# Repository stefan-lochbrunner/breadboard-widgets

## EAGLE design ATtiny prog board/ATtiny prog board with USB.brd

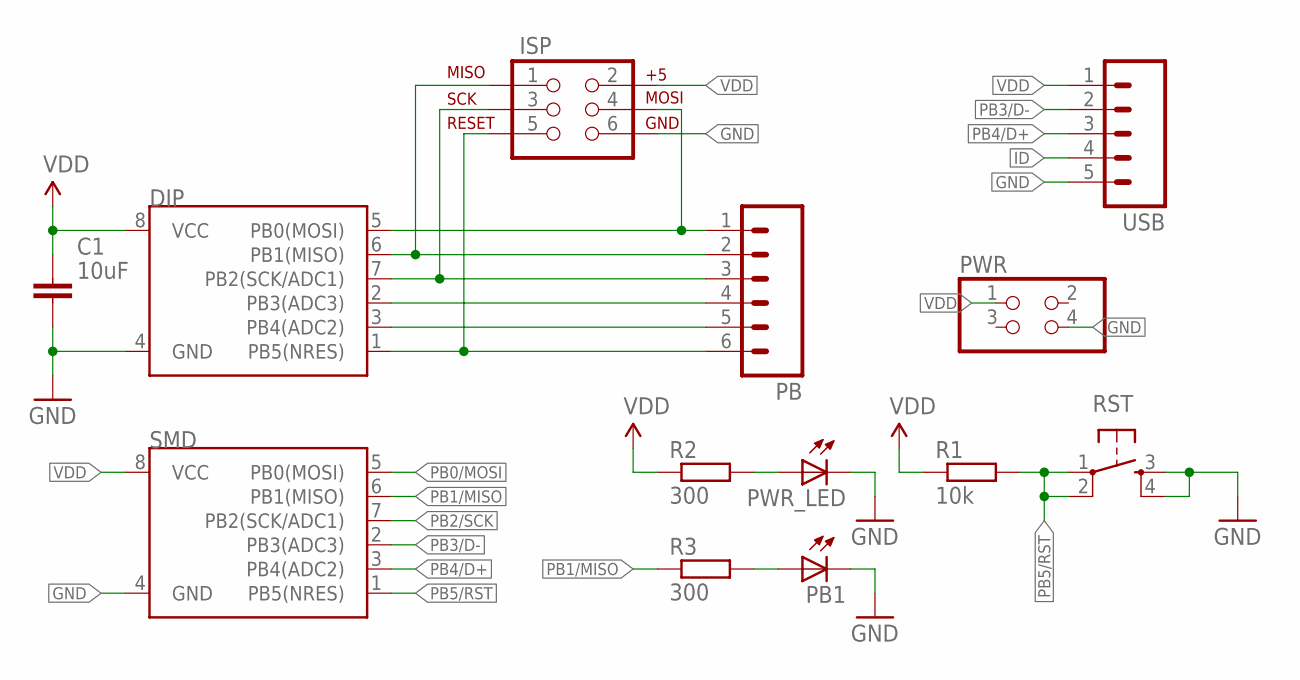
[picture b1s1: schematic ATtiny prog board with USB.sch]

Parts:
C1: 10uF; C805
DIP: ATTINY45TINY85-20-DIP; DIP08
ISP: AVR_SPI_PRG_6PTH; 2X3
PB: M06SILK_FEMALE_PTH; 1X06
PB1: LED-0805; LED-805
PWR: PINHD-2X2; 2X02
PWR_LED: LED-0805; LED-805
R1: 10k; R603
R2, R3: 300; R603
RST: TAC_SWITCHPTH; TACTILE-PTH
SMD: ATTINY45TINY85-20-SMT; SO08-EIAJ
USB: M05PTH; 1X05

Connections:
GND: C1.2, DIP.4 (GND), ISP.6, PB1.C, PWR.4, PWR_LED.C, RST.3, RST.4, SMD.4 (GND), USB.5
ID: USB.4
unnamed: PWR_LED.A, R2.2
unnamed: PB1.A, R3.2
PB0/MOSI: DIP.5 (PB0(MOSI)), ISP.4, PB.1, SMD.5 (PB0(MOSI))
PB1/MISO: DIP.6 (PB1(MISO)), ISP.1, PB.2, R3.1, SMD.6 (PB1(MISO))
PB2/SCK: DIP.7 (PB2(SCK/ADC1)), ISP.3, PB.3, SMD.7 (PB2(SCK/ADC1))
PB3/D-: DIP.2 (PB3(ADC3)), PB.4, SMD.2 (PB3(ADC3)), USB.2
PB4/D+: DIP.3 (PB4(ADC2)), PB.5, SMD.3 (PB4(ADC2)), USB.3
PB5/RST: DIP.1 (PB5(NRES)), ISP.5, PB.6, R1.2, RST.1, RST.2, SMD.1 (PB5(NRES))
VDD: C1.1, DIP.8 (VCC), ISP.2, PWR.1, R1.1, R2.1, SMD.8 (VCC), USB.1

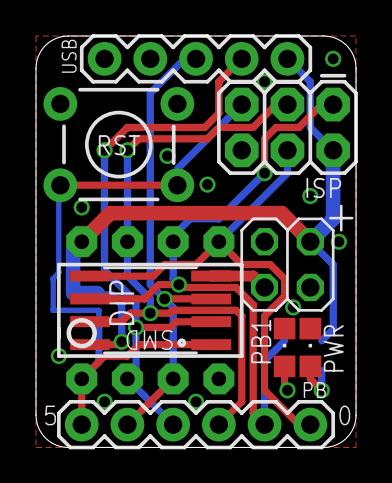
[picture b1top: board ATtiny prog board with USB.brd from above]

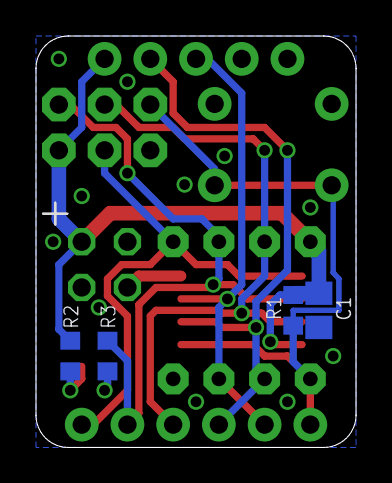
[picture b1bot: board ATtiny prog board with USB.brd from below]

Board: 2 copper layers, 17.8 x 22.9 mm, 13 parts (4 on the bottom side), 10 nets.

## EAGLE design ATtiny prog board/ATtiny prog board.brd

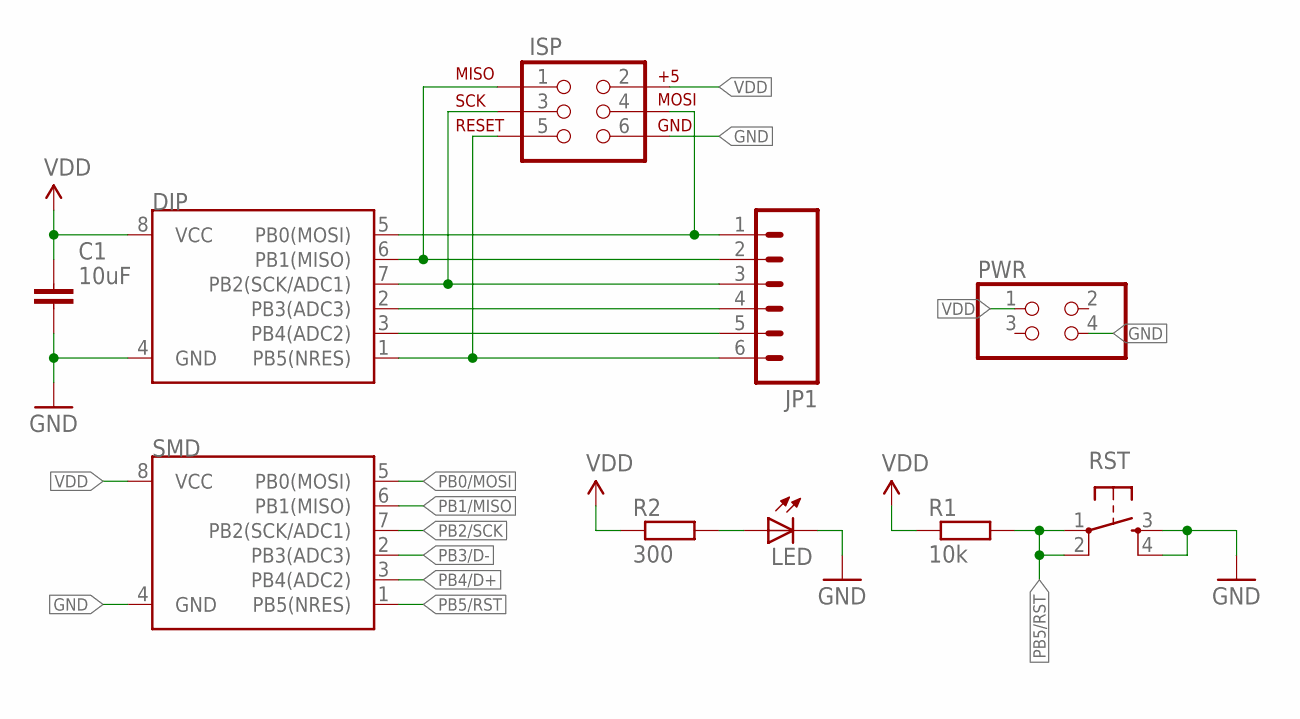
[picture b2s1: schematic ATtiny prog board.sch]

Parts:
C1: 10uF; C805
DIP: ATTINY45TINY85-20-DIP; DIP08
ISP: AVR_SPI_PRG_6PTH; 2X3
JP1: M06SILK_FEMALE_PTH; 1X06
LED: LED-0603; LED-603
PWR: PINHD-2X2; 2X02
R1: 10k; R603
R2: 300; R603
RST: TAC_SWITCHPTH; TACTILE-PTH
SMD: ATTINY45TINY85-20-SMT; SO08-EIAJ

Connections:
GND: C1.2, DIP.4 (GND), ISP.6, LED.C, PWR.4, RST.3, RST.4, SMD.4 (GND)
unnamed: LED.A, R2.2
PB0/MOSI: DIP.5 (PB0(MOSI)), ISP.4, JP1.1, SMD.5 (PB0(MOSI))
PB1/MISO: DIP.6 (PB1(MISO)), ISP.1, JP1.2, SMD.6 (PB1(MISO))
PB2/SCK: DIP.7 (PB2(SCK/ADC1)), ISP.3, JP1.3, SMD.7 (PB2(SCK/ADC1))
PB3/D-: DIP.2 (PB3(ADC3)), JP1.4, SMD.2 (PB3(ADC3))
PB4/D+: DIP.3 (PB4(ADC2)), JP1.5, SMD.3 (PB4(ADC2))
PB5/RST: DIP.1 (PB5(NRES)), ISP.5, JP1.6, R1.2, RST.1, RST.2, SMD.1 (PB5(NRES))
VDD: C1.1, DIP.8 (VCC), ISP.2, PWR.1, R1.1, R2.1, SMD.8 (VCC)

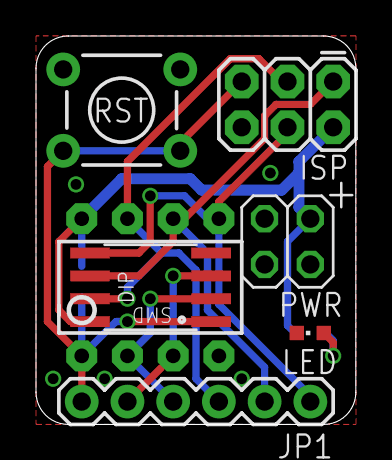
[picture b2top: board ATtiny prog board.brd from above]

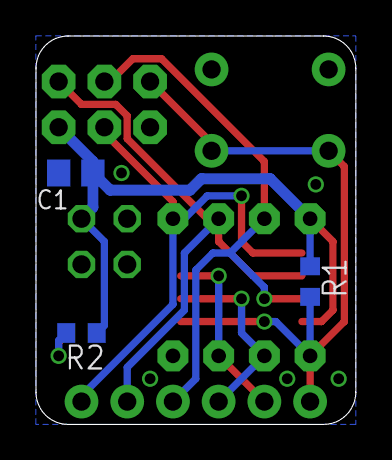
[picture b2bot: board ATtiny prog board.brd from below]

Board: 2 copper layers, 17.8 x 21.6 mm, 10 parts (3 on the bottom side), 9 nets.

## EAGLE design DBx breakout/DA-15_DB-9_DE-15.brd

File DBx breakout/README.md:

Simple breakout for DA-15, DB/DE-9 & DE-15(VGA) connectors. DB-9 to be placed on DA-15 footprint. [**more info**](https://hackaday.io/project/6332/log/26554)

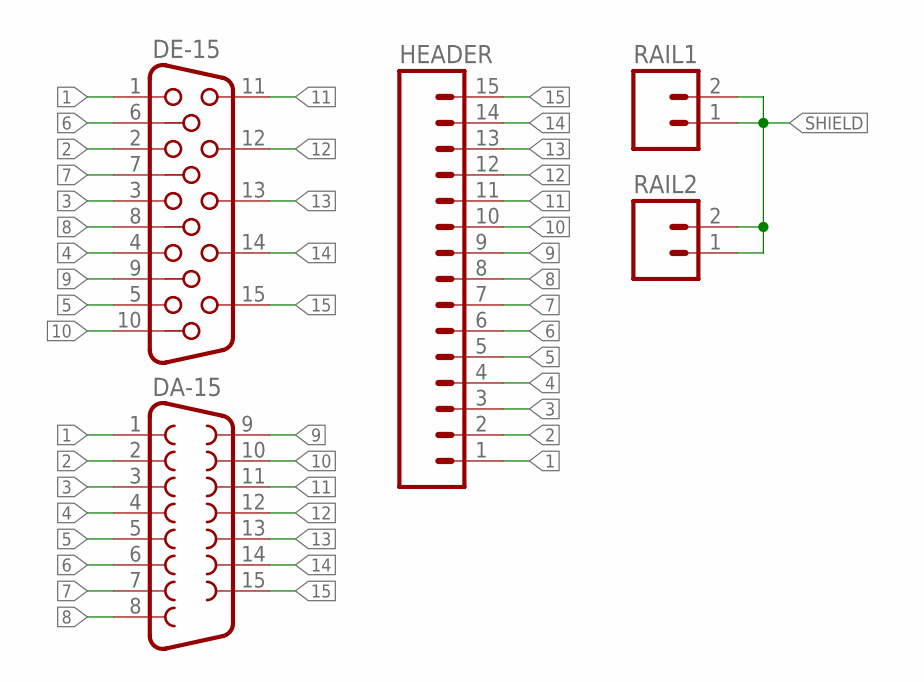
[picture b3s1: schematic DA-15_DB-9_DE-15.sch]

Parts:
DA-15: F15VB
DE-15: HF15H; HDF15H
HEADER: M15; 1X15
RAIL1, RAIL2: M02PTH; 1X02

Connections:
1: DA-15.1, DE-15.1, HEADER.1
2: DA-15.2, DE-15.2, HEADER.2
3: DA-15.3, DE-15.3, HEADER.3
4: DA-15.4, DE-15.4, HEADER.4
5: DA-15.5, DE-15.5, HEADER.5
6: DA-15.6, DE-15.6, HEADER.6
7: DA-15.7, DE-15.7, HEADER.7
8: DA-15.8, DE-15.8, HEADER.8
9: DA-15.9, DE-15.9, HEADER.9
10: DA-15.10, DE-15.10, HEADER.10
11: DA-15.11, DE-15.11, HEADER.11
12: DA-15.12, DE-15.12, HEADER.12
13: DA-15.13, DE-15.13, HEADER.13
14: DA-15.14, DE-15.14, HEADER.14
15: DA-15.15, DE-15.15, HEADER.15
SHIELD: RAIL1.1, RAIL1.2, RAIL2.1, RAIL2.2

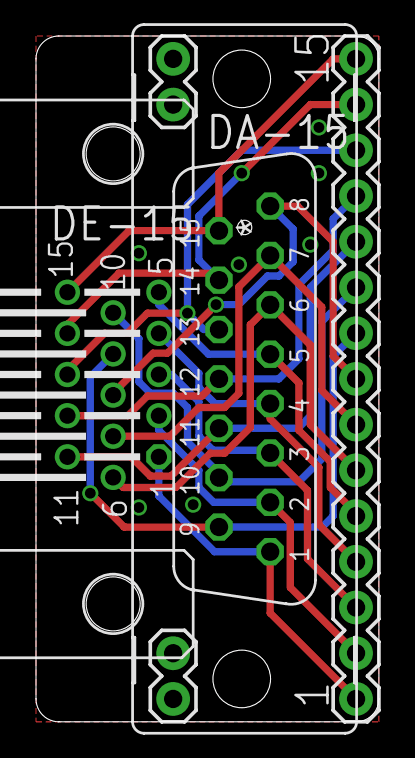
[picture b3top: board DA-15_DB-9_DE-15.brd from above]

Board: 2 copper layers, 19.1 x 38.1 mm, 5 parts (0 on the bottom side), 16 nets.

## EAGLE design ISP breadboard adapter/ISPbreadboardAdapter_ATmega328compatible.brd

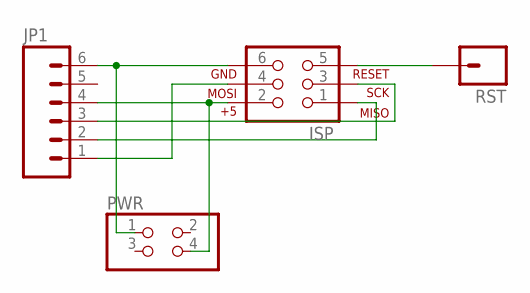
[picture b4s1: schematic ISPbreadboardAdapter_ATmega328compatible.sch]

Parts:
ISP: AVR_SPI_PRG_6PTH; 2X3
JP1: M06SILK_FEMALE_PTH; 1X06
PWR: PINHD-2X2; 2X02
RST: M01PTH; 1X01

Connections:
GND: ISP.6, JP1.6, PWR.1
MISO: ISP.1, JP1.2
MOSI: ISP.4, JP1.1
RST: ISP.5, RST.1
SCK: ISP.3, JP1.3
VCC: ISP.2, JP1.4, PWR.4

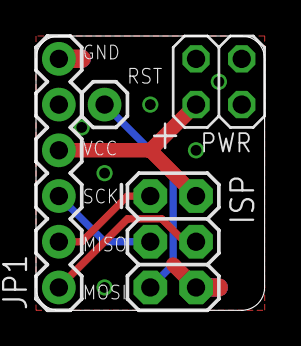
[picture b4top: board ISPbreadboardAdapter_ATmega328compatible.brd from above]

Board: 2 copper layers, 12.7 x 15.2 mm, 4 parts (0 on the bottom side), 6 nets.

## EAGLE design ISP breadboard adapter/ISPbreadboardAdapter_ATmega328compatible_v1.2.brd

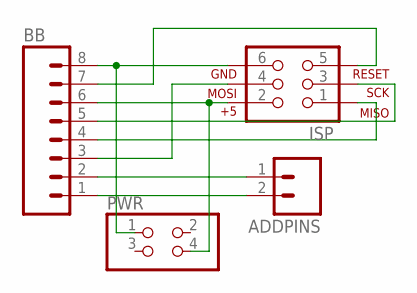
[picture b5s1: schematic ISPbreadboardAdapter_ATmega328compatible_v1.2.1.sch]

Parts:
ADDPINS: M02PTH; 1X02
BB: M08; 1X08_ROUND
ISP: AVR_SPI_PRG_6PTH; 2X3
PWR: PINHD-2X2; 2X02

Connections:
GND: BB.8, ISP.6, PWR.1
MISO: BB.4, ISP.1
MOSI: BB.3, ISP.4
unnamed: ADDPINS.1, BB.2
unnamed: ADDPINS.2, BB.1
RST: BB.7, ISP.5
SCK: BB.5, ISP.3
VCC: BB.6, ISP.2, PWR.4

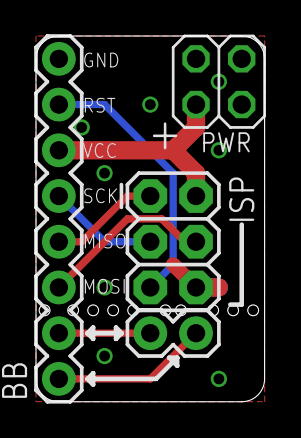
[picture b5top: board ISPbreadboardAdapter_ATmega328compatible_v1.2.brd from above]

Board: 2 copper layers, 12.7 x 20.3 mm, 4 parts (0 on the bottom side), 8 nets.

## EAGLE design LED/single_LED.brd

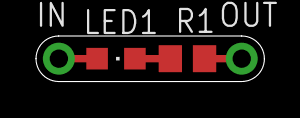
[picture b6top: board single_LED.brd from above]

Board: 2 copper layers, 12.7 x 2.5 mm, 4 parts (0 on the bottom side), 3 nets.

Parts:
IN: 1X01-CLEANBIG
LED1: LED-805
OUT: 1X01-CLEANBIG
R1: R805

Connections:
IN: IN.1, LED1.A
unnamed: LED1.C, R1.2
OUT: OUT.1, R1.1

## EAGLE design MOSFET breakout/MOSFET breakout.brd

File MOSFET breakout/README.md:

DPAK MOSFET breakout to be used as single channel PWM driver. Footprint should also fit SOT-223 package where pin 2 is internally connected to tab.
[**more info**](https://hackaday.io/project/6332-breadboard-widgets/log/21781-mosfet-breakout-for-pwm-driver)

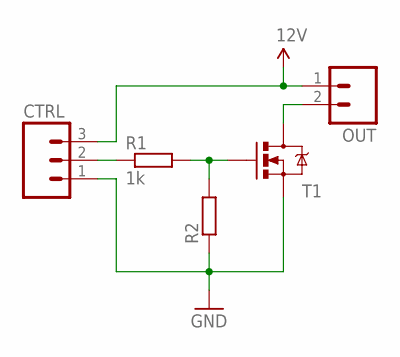
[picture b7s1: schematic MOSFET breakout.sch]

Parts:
CTRL: M03PTH; 1X03
OUT: M02PTH; 1X02
R1: 1k; R603
R2: RESISTOR-0603; R603
T1: MOSFET-NCHANNELFDD8780; DPAK

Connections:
12V: CTRL.3, OUT.1
GND: CTRL.1, R2.1, T1.3 (S)
unnamed: R1.2, R2.2, T1.1 (G)
unnamed: CTRL.2, R1.1
unnamed: OUT.2, T1.4 (D)

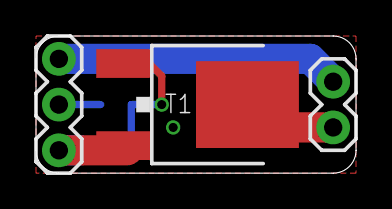
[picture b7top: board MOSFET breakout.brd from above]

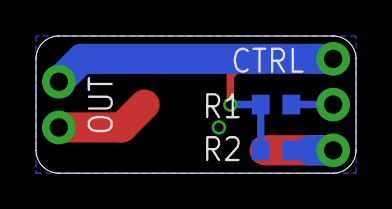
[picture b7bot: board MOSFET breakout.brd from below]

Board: 2 copper layers, 17.8 x 7.6 mm, 5 parts (2 on the bottom side), 5 nets.

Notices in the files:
parts and their libraries:
SparkFun-DigitalIC: Licensing: Creative Commons ShareAlike 4.0 International - https://creativecommons.org/licenses/by-sa/4.0
SparkFun-Connectors: Licensing: CC v3.0 Share-Alike You are welcome to use this library for commercial purposes.
